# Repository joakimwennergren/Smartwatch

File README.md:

<!-- PROJECT LOGO -->
<br />
<div align="center">
  
<h3>Smartwatch</h3>

</div>

<!-- ABOUT THE PROJECT -->

## About The Project

This project is the development of a next-generation smartwatch designed for both style and functionality. Powered by FreeRTOS, it offers a responsive, real-time operating environment optimized for wearable technology.

Key features include:

SUOTA (Software Upgrade Over The Air) for seamless firmware updates without cables.

Wireless charging for hassle-free power replenishment.

A 368x448 AMOLED display delivering vibrant colors, deep blacks, and excellent outdoor visibility.

Integrated IMU (Inertial Measurement Unit) for accurate motion tracking.

Bluetooth Low Energy 5.2 connectivity for reliable, energy-efficient communication.

The smartwatch will support core functions such as precise timekeeping, step counting, and additional health and activity monitoring features. With its combination of advanced hardware and efficient real-time software, this device aims to deliver a smooth user experience while maintaining low power consumption for extended battery life.

<p align="right">(<a href="#readme-top">back to top</a>)</p>

<!-- LICENSE -->

## License

Distributed under the MIT License. See `LICENSE.txt` for more information.

<p align="right">(<a href="#readme-top">back to top</a>)</p>

<!-- CONTACT -->

## Contact

Joakim Wennergren - joakim.wennergren@databeams.se

<p align="right">(<a href="#readme-top">back to top</a>)</p>

<!-- ACKNOWLEDGMENTS -->

## Acknowledgments

Useful resources while creating this project.

* https://www.aliexpress.com/i/1005005269549886.html - Display connector
* https://www.molex.com/en-us/products/part-detail/559092474?display=pdf - molex connector
* https://www.3dcontentcentral.com/Search.aspx?arg=OK-14GM024-04&SortBy=match&PageSize=10 - display connector 3D
* https://www.device-center.com/ok-14gm024-04 - display connector

<p align="right">(<a href="#readme-top">back to top</a>)</p>

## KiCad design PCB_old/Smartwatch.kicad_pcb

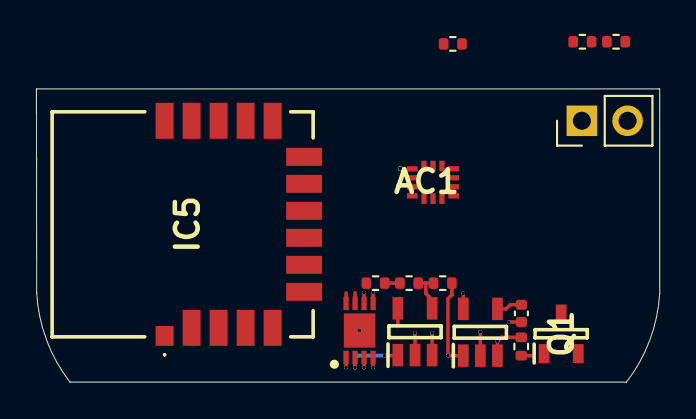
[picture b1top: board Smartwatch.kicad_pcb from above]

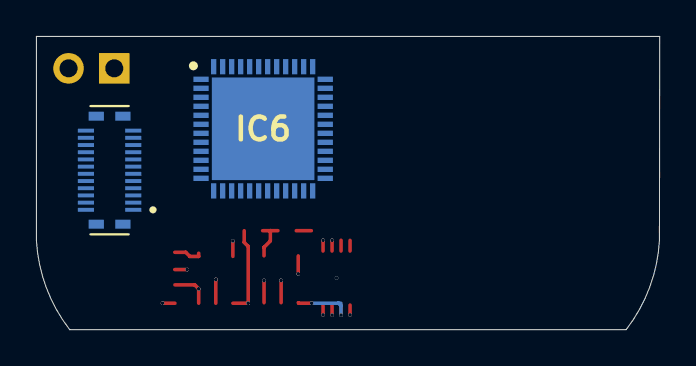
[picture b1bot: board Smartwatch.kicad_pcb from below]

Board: 6 copper layers, 34.6 x 16.3 mm, 17 parts (2 on the bottom side), 15 nets.

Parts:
AC1: LSM6DSOXTR; LGA-14_1
C1: 1µF; C_0402_1005Metric
IC1: SOT95P280X145-5N
IC2: MAX9064EUK+T; SOT95P280X145-5N
IC4: MAX17040G+T; SON50P300X200X80-9N
IC5: DA14531MOD-00F01002; DA14531MOD00F01002
IC6: STM32U575CIU6Q; QFN50P700X700X60-49N-D
J1: OK-14GM024-04
J3: VBATT; PinHeader_1x02_P2.54mm_Vertical
Q1: PMV65XPVL; SOT95P230X110-3N
R1, R5#2: 10K; R_0402_1005Metric
R2: 4.32K; R_0402_1005Metric
R3: 1M; R_0402_1005Metric
R4: 100K; R_0402_1005Metric
R5, R6: 4.7K; R_0402_1005Metric

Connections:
+3V3: AC1.1 (SDO/SA0), AC1.2 (SDX), AC1.3 (SCX), AC1.5 (VDDIO), AC1.8 (VDD), AC1.12 (CS), IC1.5 (VOUT), IC4.3 (VDD), IC5.J7 (VBAT), IC6.1 (VBAT), IC6.9 (VDDA), IC6.25 (VDD_1), IC6.36 (VDD_2), IC6.48 (VDD_3), R5.1, R6.1
BOOT0: IC5.J16 (P0_8), IC6.44 (PH3-BOOT0), R5#2.2
GND: AC1.6 (GND_1), AC1.7 (GND_2), C1.2, IC1.2 (GND), IC2.2 (GND_1), IC2.3 (GND_2), IC4.1 (CTG), IC4.4 (GND), IC4.5 (SEO), IC4.6 (EO), IC4.9 (EP), IC5.J2 (GND_1), IC5.J3 (GND_2), IC5.J4 (GND_3), IC5.J6 (GND_4), IC5.J11 (GND_5), IC6.8 (VSSA), IC6.21 (VDDSMPS), IC6.22 (VSSSMPS), IC6.24 (VSS_1), IC6.35 (VSS_2), IC6.47 (VSS_3), IC6.49 (EP), J3.1, R3.2, R5#2.1
I2C_SCL: AC1.13 (SCL), IC4.7 (SCL), IC6.26 (PB13), R6.2
I2C_SDA: AC1.14 (SDA), IC4.8 (SDA), IC6.27 (PB14), R5.2
IMU_INT1: AC1.4 (INT1), IC6.28 (PB15)
IMU_INT2: AC1.9 (INT2), IC6.29 (PA8)
NRST: IC5.J15 (P0_9), IC6.7 (NRST)
unnamed: C1.1, IC1.4 (BYPASS)
unnamed: IC2.4 (IN), R1.2, R2.1
unnamed: R2.2, R3.1
SHDN: IC1.3 (~SHDN), IC2.5 (OUT), R4.2
UART_MCU_RX: IC5.J5 (P0_6), IC6.31 (PA10)
UART_MCU_TX: IC5.J14 (P0_5/RXTX), IC6.30 (PA9)
VBATT: IC1.1 (VIN), IC2.1 (REF(VCC)), IC4.2 (CELL), J3.2, R1.1, R4.1

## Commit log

2025-08-10 jpg not jpeg
2025-08-10 Add LICENSE.txt
2025-08-10 Add Display initialization code
2025-08-10 Add LVGL
2025-08-10 Add LVGL and remove history from cube ide
2025-08-10 Add initialization code for LVGL
2025-08-10 README.md
2025-08-10 Add boiler for CST820
2025-08-29 Add bench and new PCB
2025-08-30 FreeRTOS
2025-08-30 Cleanup
2025-08-30 Cleaning
